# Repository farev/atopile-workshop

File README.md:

# workshop

Workshop project

Created by Fabian <fabiareor@gmail.com>

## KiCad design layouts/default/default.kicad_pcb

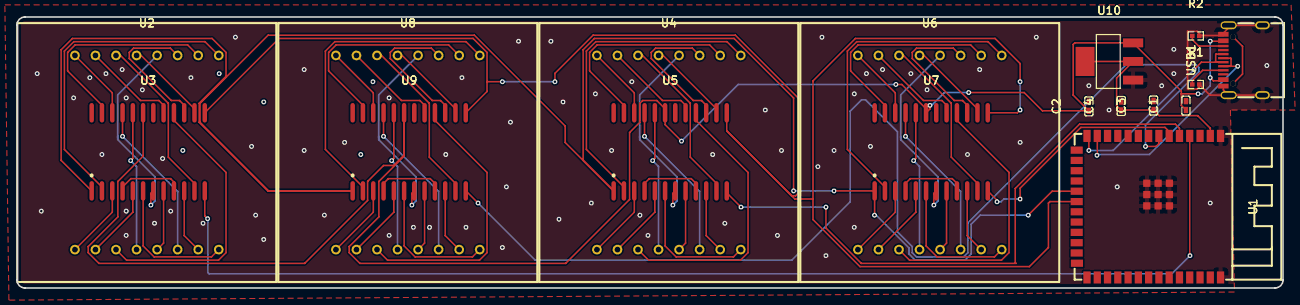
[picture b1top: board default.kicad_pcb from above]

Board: 2 copper layers, 156.5 x 33.5 mm, 17 parts (0 on the bottom side), 81 nets.

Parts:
C1, C2, C3, C4: 1µF ±10% 25V X5R; C0402
R1, R2: 5.1kΩ ±1% 62.5mW; R0402
U1: WIRELM-SMD_ESP32-S3-WROOM-1
U2, U4, U6, U8: LED-SEG-TH_SZ421288N-64
U3, U5, U7, U9: SOP-24_L15.4-W7.5-P1.27-LS10.4-BL
U10: SOT-223-3_L6.5-W3.4-P2.30-LS7.0-BR
USB1: USB-C-SMD_KH-TYPE-C-16P

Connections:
B5: R2.1, USB1.B5
CC1: R1.1, USB1.A5
DIG0: U2.9, U3.2
DIG5: U4.7, U5.10
IO19: U1.13, USB1.A7, USB1.B7
IO20: U1.14, USB1.A6, USB1.B6
ROW2: U8.14, U9.11
ROW3: U4.8, U5.6
ROW4: U6.12, U7.7
ROW5: U4.1, U5.3
Vpos: C1.1, C2.1, U3.19, U5.19, U7.19, U9.19, U10.3, USB1.A4, USB1.A9, USB1.B4, USB1.B9
clk: U1.20, U3.13, U5.13, U7.13, U9.13
cs: U1.4, U3.12
cs-1: U1.7, U9.12
cs-2: U1.5, U5.12
cs-3: U1.6, U7.12
din: U1.19, U3.1, U5.1, U7.1, U9.1
display1-DIG1: U2.14, U3.11
display1-DIG2: U2.8, U3.6
display1-DIG3: U2.12, U3.7
display1-DIG4: U2.1, U3.3
display1-DIG6: U2.2, U3.5
display1-ROW6: U2.7, U3.10
display1-ROW8: U2.5, U3.8
display1-SEGA: U2.13, U3.14
display1-SEGB: U2.3, U3.16
display1-SEGC: U2.4, U3.20
display1-SEGD: U2.10, U3.23
display1-SEGDP: U2.16, U3.22
display1-SEGE: U2.6, U3.21
display1-SEGF: U2.11, U3.15
display1-SEGG: U2.15, U3.17
display1-gnd: U3.4, U3.9
display2-DIG1: U4.14, U5.11
display2-DIG3: U4.12, U5.7
display2-DIG7: U4.5, U5.8
display2-ROW1: U4.9, U5.2
display2-ROW7: U4.2, U5.5
display2-SEGA: U4.13, U5.14
display2-SEGB: U4.3, U5.16
display2-SEGC: U4.4, U5.20
display2-SEGD: U4.10, U5.23
display2-SEGDP: U4.16, U5.22
display2-SEGE: U4.6, U5.21
display2-SEGF: U4.11, U5.15
display2-SEGG: U4.15, U5.17
display2-gnd: U5.4, U5.9
display3-DIG1: U6.14, U7.11
display3-DIG2: U6.8, U7.6
display3-DIG4: U6.1, U7.3
display3-DIG7: U6.5, U7.8
display3-ROW1: U6.9, U7.2
display3-ROW6: U6.7, U7.10
display3-ROW7: U6.2, U7.5
display3-SEGA: U6.13, U7.14
display3-SEGB: U6.3, U7.16
display3-SEGC: U6.4, U7.20
display3-SEGD: U6.10, U7.23
display3-SEGDP: U6.16, U7.22
display3-SEGE: U6.6, U7.21
display3-SEGF: U6.11, U7.15
display3-SEGG: U6.15, U7.17
display3-gnd: U7.4, U7.9
display4-DIG2: U8.8, U9.6
display4-DIG3: U8.12, U9.7
display4-DIG4: U8.1, U9.3
display4-DIG6: U8.2, U9.5
display4-ROW1: U8.9, U9.2
display4-ROW6: U8.7, U9.10
display4-ROW8: U8.5, U9.8
display4-SEGA: U8.13, U9.14
display4-SEGB: U8.3, U9.16
display4-SEGC: U8.4, U9.20
display4-SEGD: U8.10, U9.23
display4-SEGDP: U8.16, U9.22
display4-SEGE: U8.6, U9.21
display4-SEGF: U8.11, U9.15
display4-SEGG: U8.15, U9.17
display4-gnd: U9.4, U9.9
gnd: C1.2, C2.2, C3.2, C4.2, R1.2, R2.2, U1.1, U1.40, U1.41, U10.1, USB1.1, USB1.2, USB1.3, USB1.4, USB1.A1, USB1.A12, USB1.B1, USB1.B12
hv: C3.1, C4.1, U1.2, U10.2, U10.4

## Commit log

2025-06-18 Initial commit: Add workshop project with layouts and main files
2025-06-18 Making sure everything is correct
2025-06-18 Fix parts in gitignore
